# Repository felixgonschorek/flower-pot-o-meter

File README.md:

# flower-pot-o-meter
Watering my plants IoT style with nRF24, cheap 3V water pumps from china, a Raspberry PI, MQTT and everyhting i could pack in this setup

## File overview

- chronograf: folder with chronograf, telegraf and influx for logging and visualizing sensor data
- Makefile: to build c++ program on raspberry pi
- flower-pot-o-meter.ino: Arduino project file
- fpom.cpp: c++ Program for rPI
- frpom.h: common header file for rPI and arduino

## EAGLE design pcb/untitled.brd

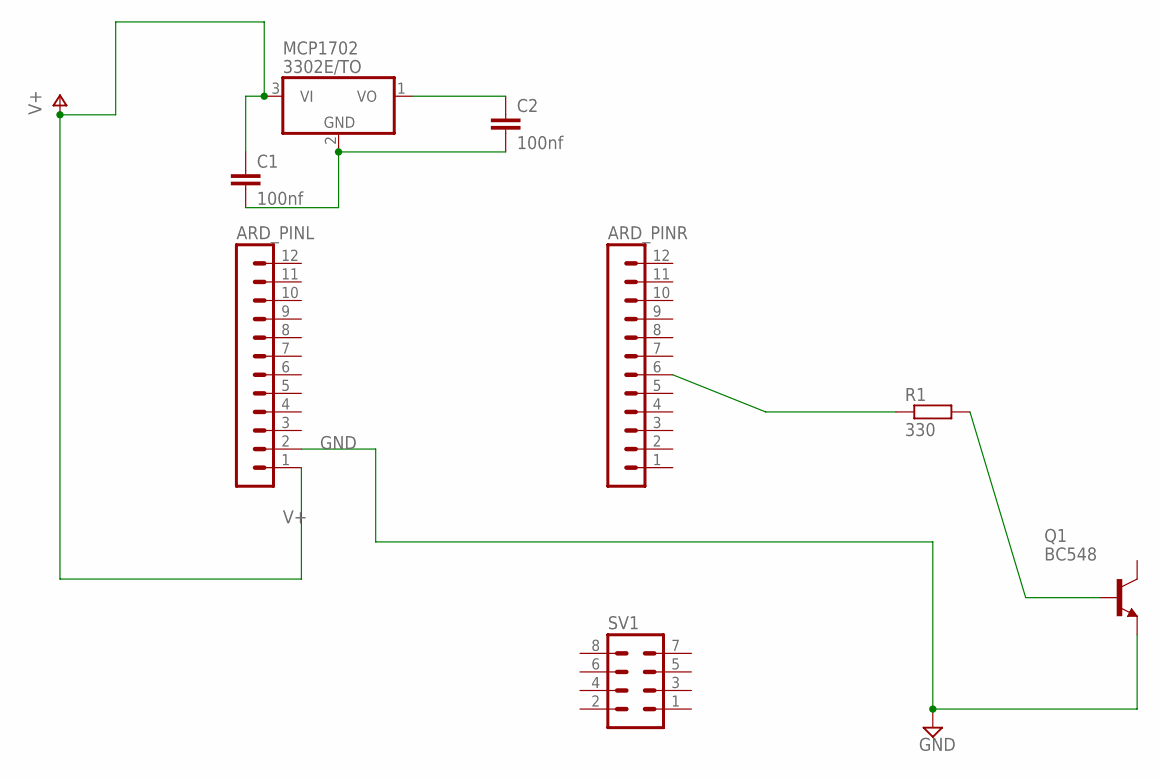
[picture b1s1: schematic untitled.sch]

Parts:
ARD_PINL: MA12-1
ARD_PINR: MA12-1
C1, C2: 100nf; C025-024X044
MCP1702: 3302E/TO; TO92
Q1: BC548; TO92-EBC
R1: 330; 0204V
SV1: MA04-2

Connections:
GND: ARD_PINL.2, Q1.E
unnamed: ARD_PINR.6, R1.1
unnamed: Q1.B, R1.2
unnamed: C2.1, MCP1702.1 (VO)
unnamed: C1.2, C2.2, MCP1702.2 (GND)
V+: ARD_PINL.1, C1.1, MCP1702.3 (VI)

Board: 2 copper layers, 8 parts (0 on the bottom side), 6 nets, no tracks yet.

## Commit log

2018-05-13 add '.project' to .gitignore
2018-05-13 add arduino files, add regular common header file
2018-05-13 add header include for fpom.h in fpom.cpp
2018-05-13 add node red workflow (wip)
2018-05-13 improve logging visibility
2018-05-13 wip: eagle schematics
2018-05-14 power moisture sensor only when needed
2018-05-25 wip: try to fix problems with 3v submerged pump
2018-06-19 add .gitignore
2018-06-19 fix imports
2018-06-26 add battery management
2018-07-01 resubscribe to topics on disconnect
2018-07-01 chronograf: add restart policy to services
2018-07-02 increase wait time
